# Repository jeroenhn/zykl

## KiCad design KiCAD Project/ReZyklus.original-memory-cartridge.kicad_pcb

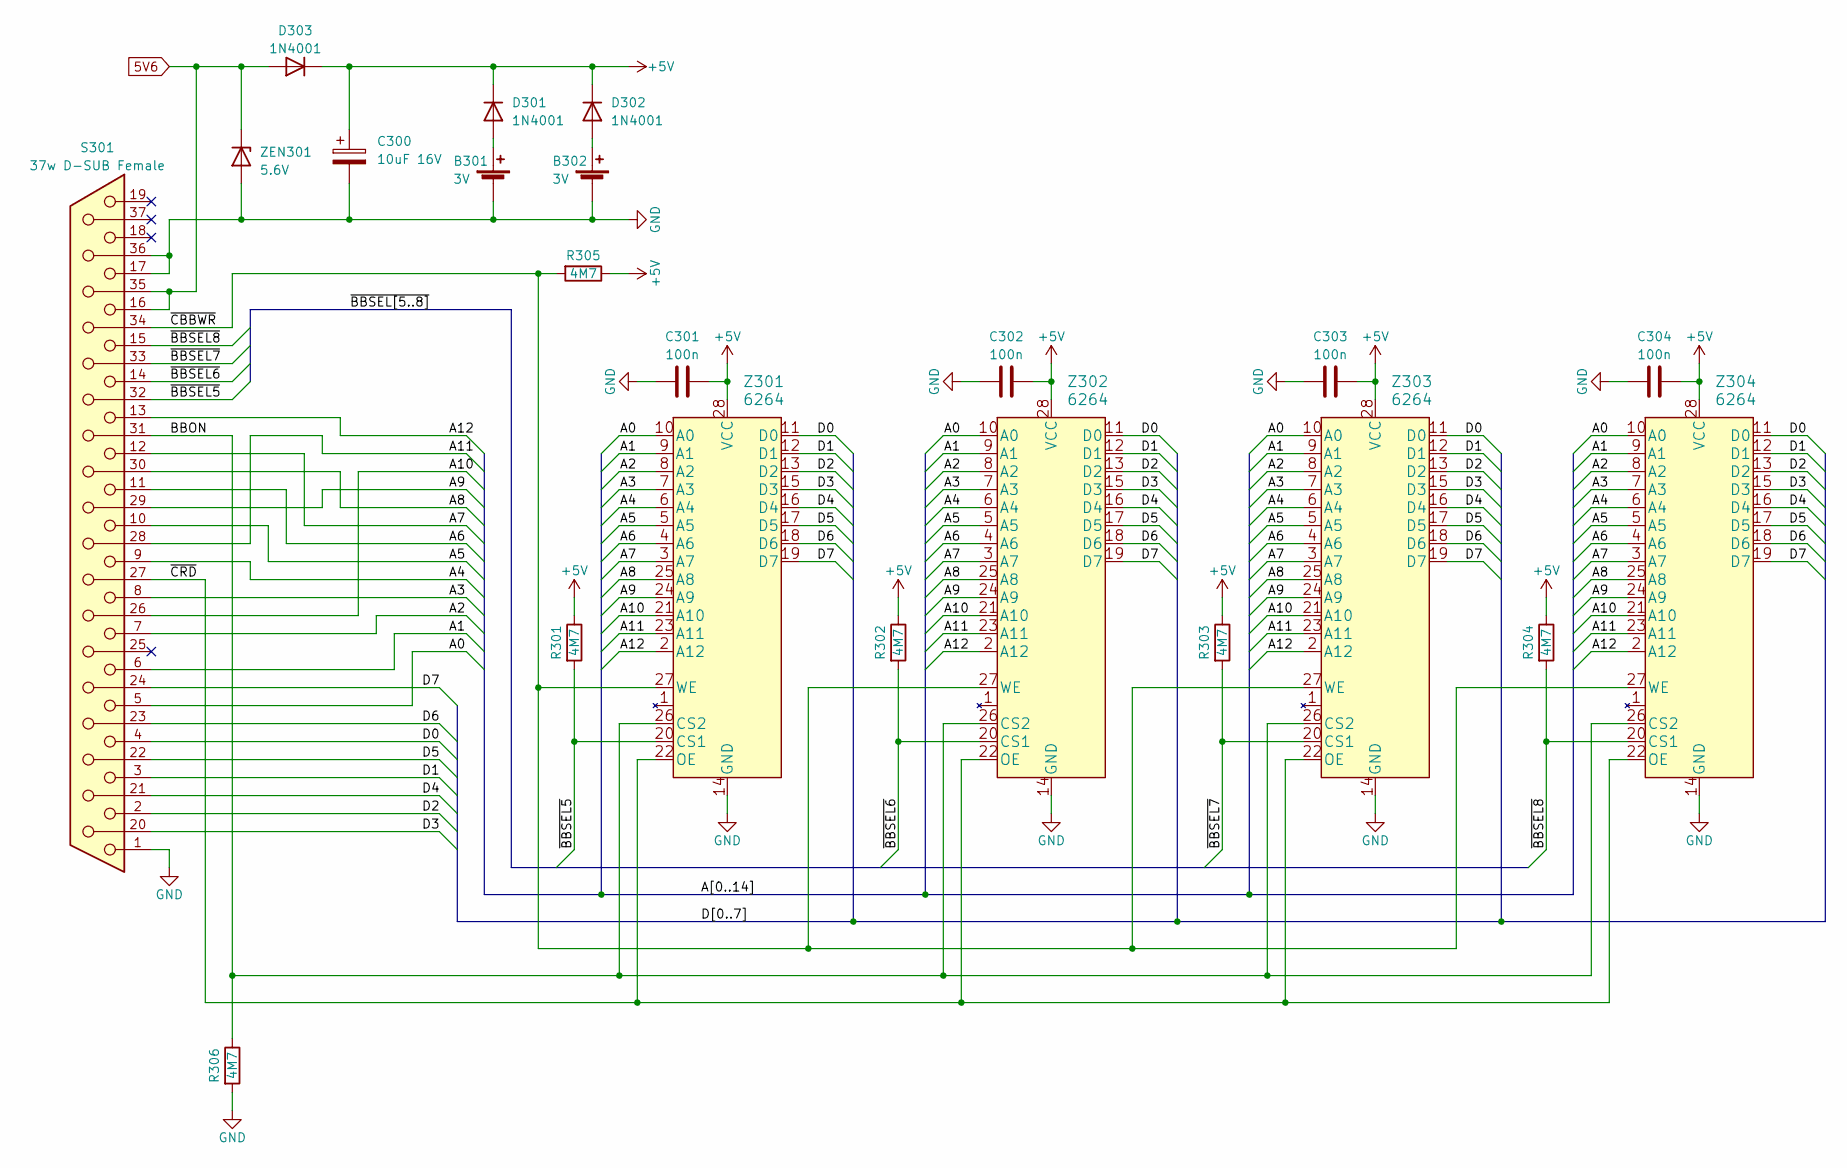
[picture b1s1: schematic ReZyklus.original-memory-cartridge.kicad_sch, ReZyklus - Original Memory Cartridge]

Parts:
B301, B302: 3V; Half-AA-Cell-Holder
C300: 10uF 16V; CP_Elec_5x5.8
C301, C302, C303, C304: 100n; C_1206_3216Metric
D301, D302, D303: 1N4001; D_SMA
R301, R302, R303, R304, R305, R306: 4M7; R_1206_3216Metric
S301: 37w D-SUB Female; DSUB-37_Female_Horizontal_P2.77x2.84mm_EdgePinOffset7.70mm_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
Z301, Z302, Z303, Z304: 6264; DIP-28_W15.24mm_Socket_LongPads
ZEN301: 5.6V; D_SMA

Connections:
5V6: D303.2 (A), S301.16, S301.35, ZEN301.1 (K)
+5V: C300.1, C301.2, C302.2, C303.2, C304.2, D301.1 (K), D302.1 (K), D303.1 (K), R301.1, R302.1, R303.1, R304.1, R305.1, Z301.28 (VCC), Z302.28 (VCC), Z303.28 (VCC), Z304.28 (VCC)
/A0: S301.5, Z301.10 (A0), Z302.10 (A0), Z303.10 (A0), Z304.10 (A0)
/A1: S301.6, Z301.9 (A1), Z302.9 (A1), Z303.9 (A1), Z304.9 (A1)
/A2: S301.7, Z301.8 (A2), Z302.8 (A2), Z303.8 (A2), Z304.8 (A2)
/A3: S301.8, Z301.7 (A3), Z302.7 (A3), Z303.7 (A3), Z304.7 (A3)
/A4: S301.9, Z301.6 (A4), Z302.6 (A4), Z303.6 (A4), Z304.6 (A4)
/A5: S301.10, Z301.5 (A5), Z302.5 (A5), Z303.5 (A5), Z304.5 (A5)
/A6: S301.11, Z301.4 (A6), Z302.4 (A6), Z303.4 (A6), Z304.4 (A6)
/A7: S301.12, Z301.3 (A7), Z302.3 (A7), Z303.3 (A7), Z304.3 (A7)
/A8: S301.30, Z301.25 (A8), Z302.25 (A8), Z303.25 (A8), Z304.25 (A8)
/A9: S301.29, Z301.24 (A9), Z302.24 (A9), Z303.24 (A9), Z304.24 (A9)
/A10: S301.26, Z301.21 (A10), Z302.21 (A10), Z303.21 (A10), Z304.21 (A10)
/A11: S301.28, Z301.23 (A11), Z302.23 (A11), Z303.23 (A11), Z304.23 (A11)
/A12: S301.13, Z301.2 (A12), Z302.2 (A12), Z303.2 (A12), Z304.2 (A12)
/BBON: R306.1, S301.31, Z301.26 (CS2), Z302.26 (CS2), Z303.26 (CS2), Z304.26 (CS2)
/D0: S301.4, Z301.11 (D0), Z302.11 (D0), Z303.11 (D0), Z304.11 (D0)
/D1: S301.3, Z301.12 (D1), Z302.12 (D1), Z303.12 (D1), Z304.12 (D1)
/D2: S301.2, Z301.13 (D2), Z302.13 (D2), Z303.13 (D2), Z304.13 (D2)
/D3: S301.20, Z301.15 (D3), Z302.15 (D3), Z303.15 (D3), Z304.15 (D3)
/D4: S301.21, Z301.16 (D4), Z302.16 (D4), Z303.16 (D4), Z304.16 (D4)
/D5: S301.22, Z301.17 (D5), Z302.17 (D5), Z303.17 (D5), Z304.17 (D5)
/D6: S301.23, Z301.18 (D6), Z302.18 (D6), Z303.18 (D6), Z304.18 (D6)
/D7: S301.24, Z301.19 (D7), Z302.19 (D7), Z303.19 (D7), Z304.19 (D7)
/~BBSEL5: R301.2, S301.32, Z301.20 (CS1)
/~BBSEL6: R302.2, S301.14, Z302.20 (CS1)
/~BBSEL7: R303.2, S301.33, Z303.20 (CS1)
/~BBSEL8: R304.2, S301.15, Z304.20 (CS1)
/~CBBWR: R305.2, S301.34, Z301.27 (WE), Z302.27 (WE), Z303.27 (WE), Z304.27 (WE)
/~CRD: S301.27, Z301.22 (OE), Z302.22 (OE), Z303.22 (OE), Z304.22 (OE)
GND: B301.2 (-), B302.2 (-), C300.2, C301.1, C302.1, C303.1, C304.1, R306.2, S301.1, S301.17, S301.36, Z301.14 (GND), Z302.14 (GND), Z303.14 (GND), Z304.14 (GND), ZEN301.2 (A)
unnamed: B301.1 (+), D301.2 (A)
unnamed: B302.1 (+), D302.2 (A)

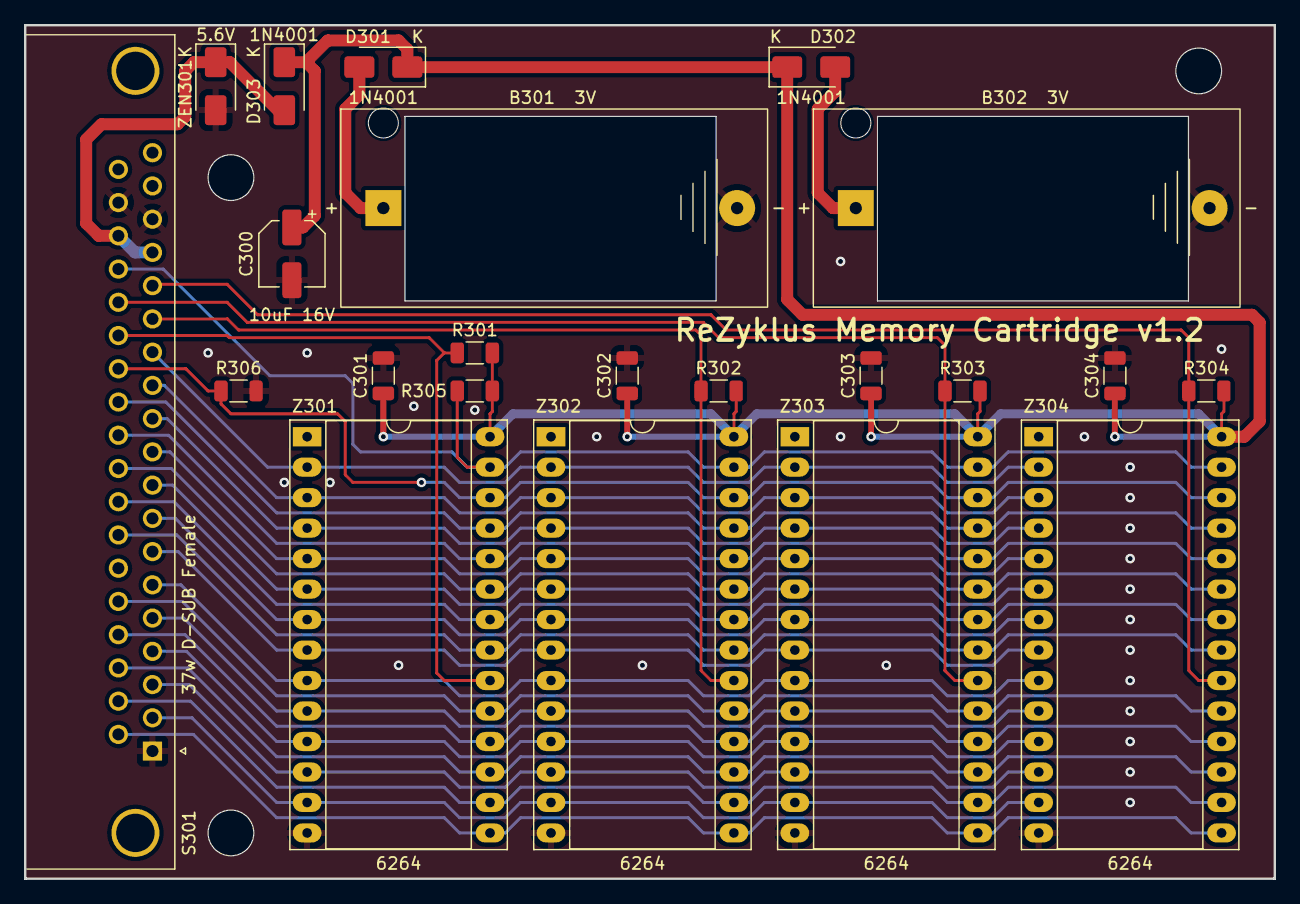
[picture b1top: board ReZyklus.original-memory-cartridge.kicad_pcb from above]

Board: 2 copper layers, 104.1 x 71.1 mm, 22 parts (0 on the bottom side), 33 nets.
